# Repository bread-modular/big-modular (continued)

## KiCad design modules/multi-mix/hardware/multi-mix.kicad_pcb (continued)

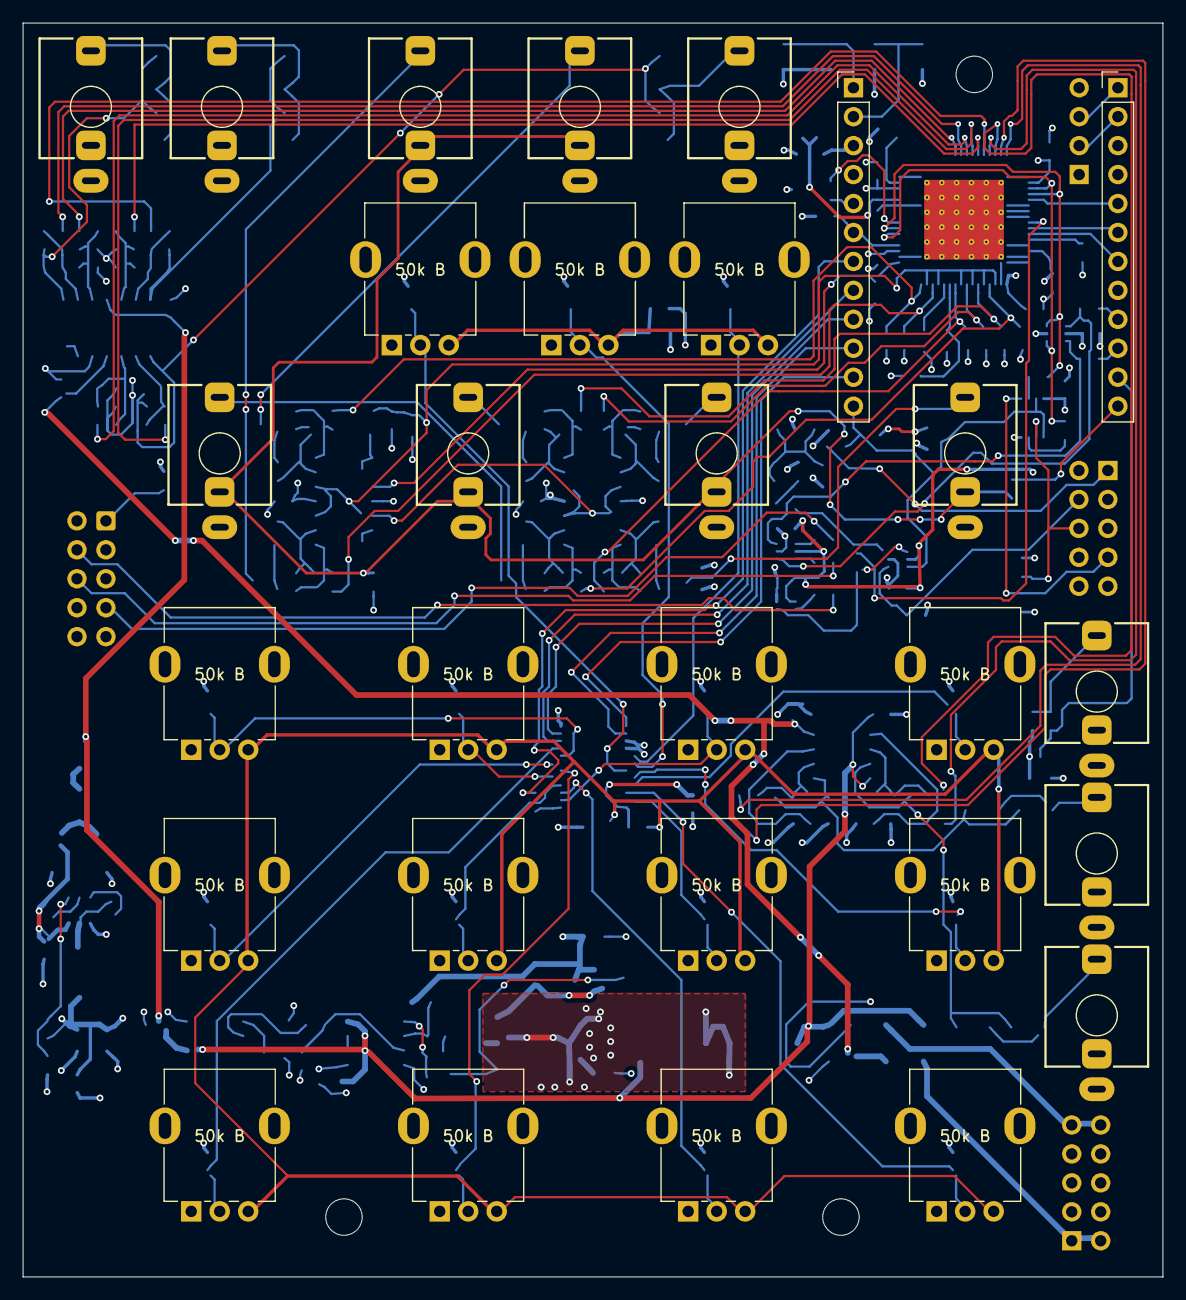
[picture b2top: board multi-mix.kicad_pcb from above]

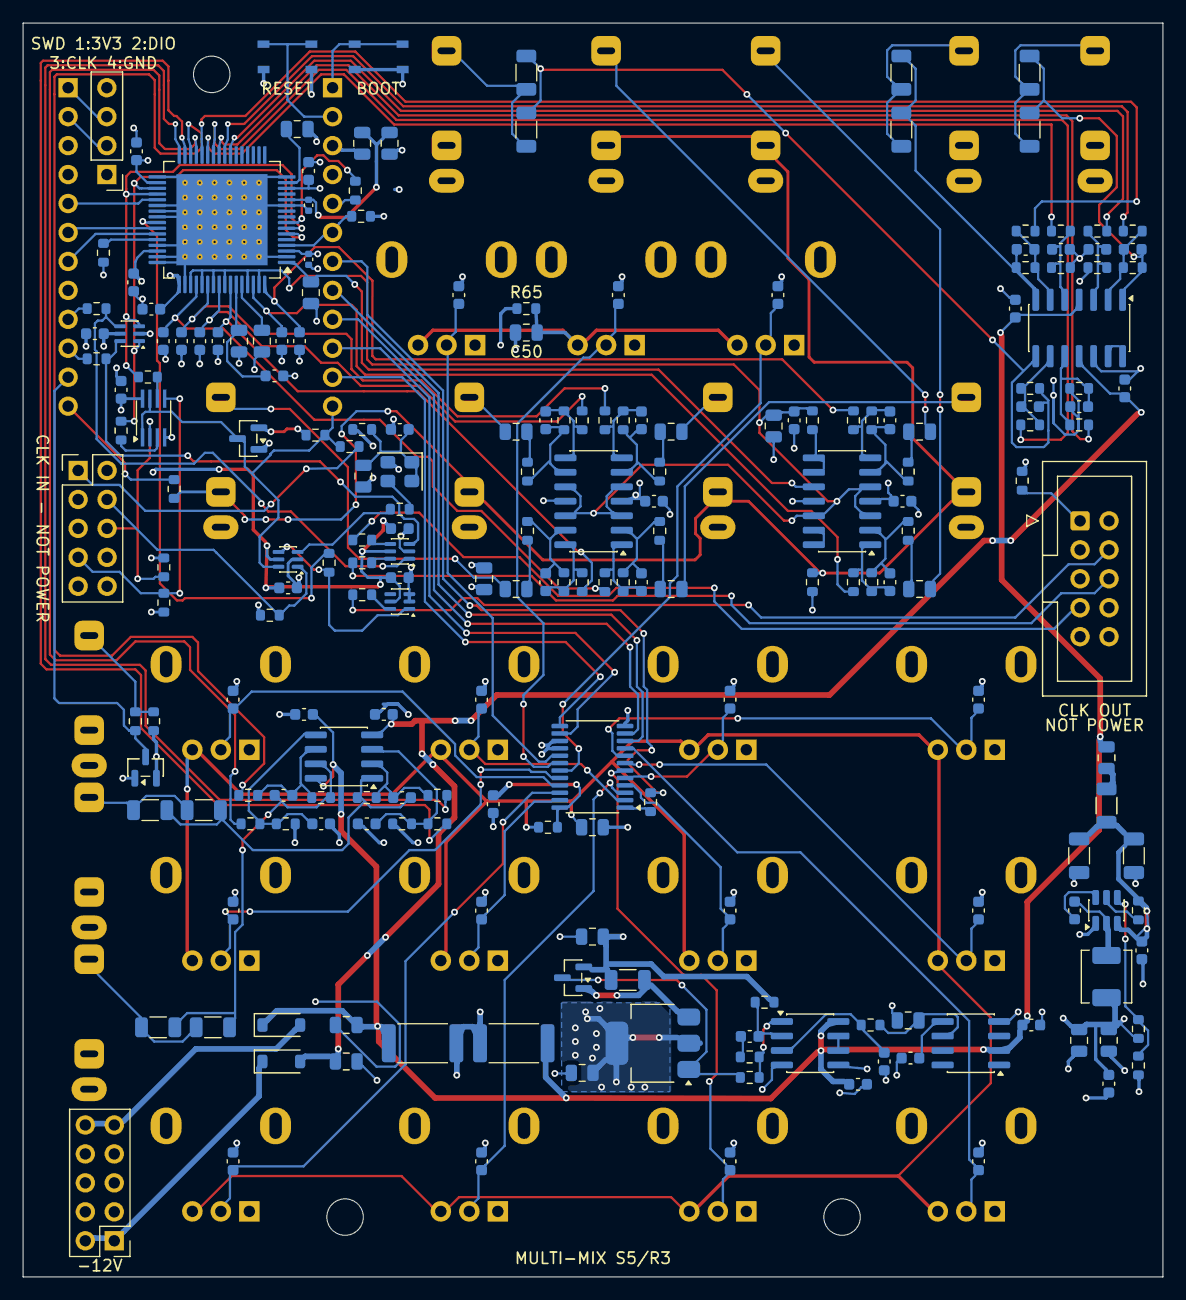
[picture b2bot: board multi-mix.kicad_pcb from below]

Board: 4 copper layers, 100.0 x 110.0 mm, 236 parts (207 on the bottom side), 155 nets.

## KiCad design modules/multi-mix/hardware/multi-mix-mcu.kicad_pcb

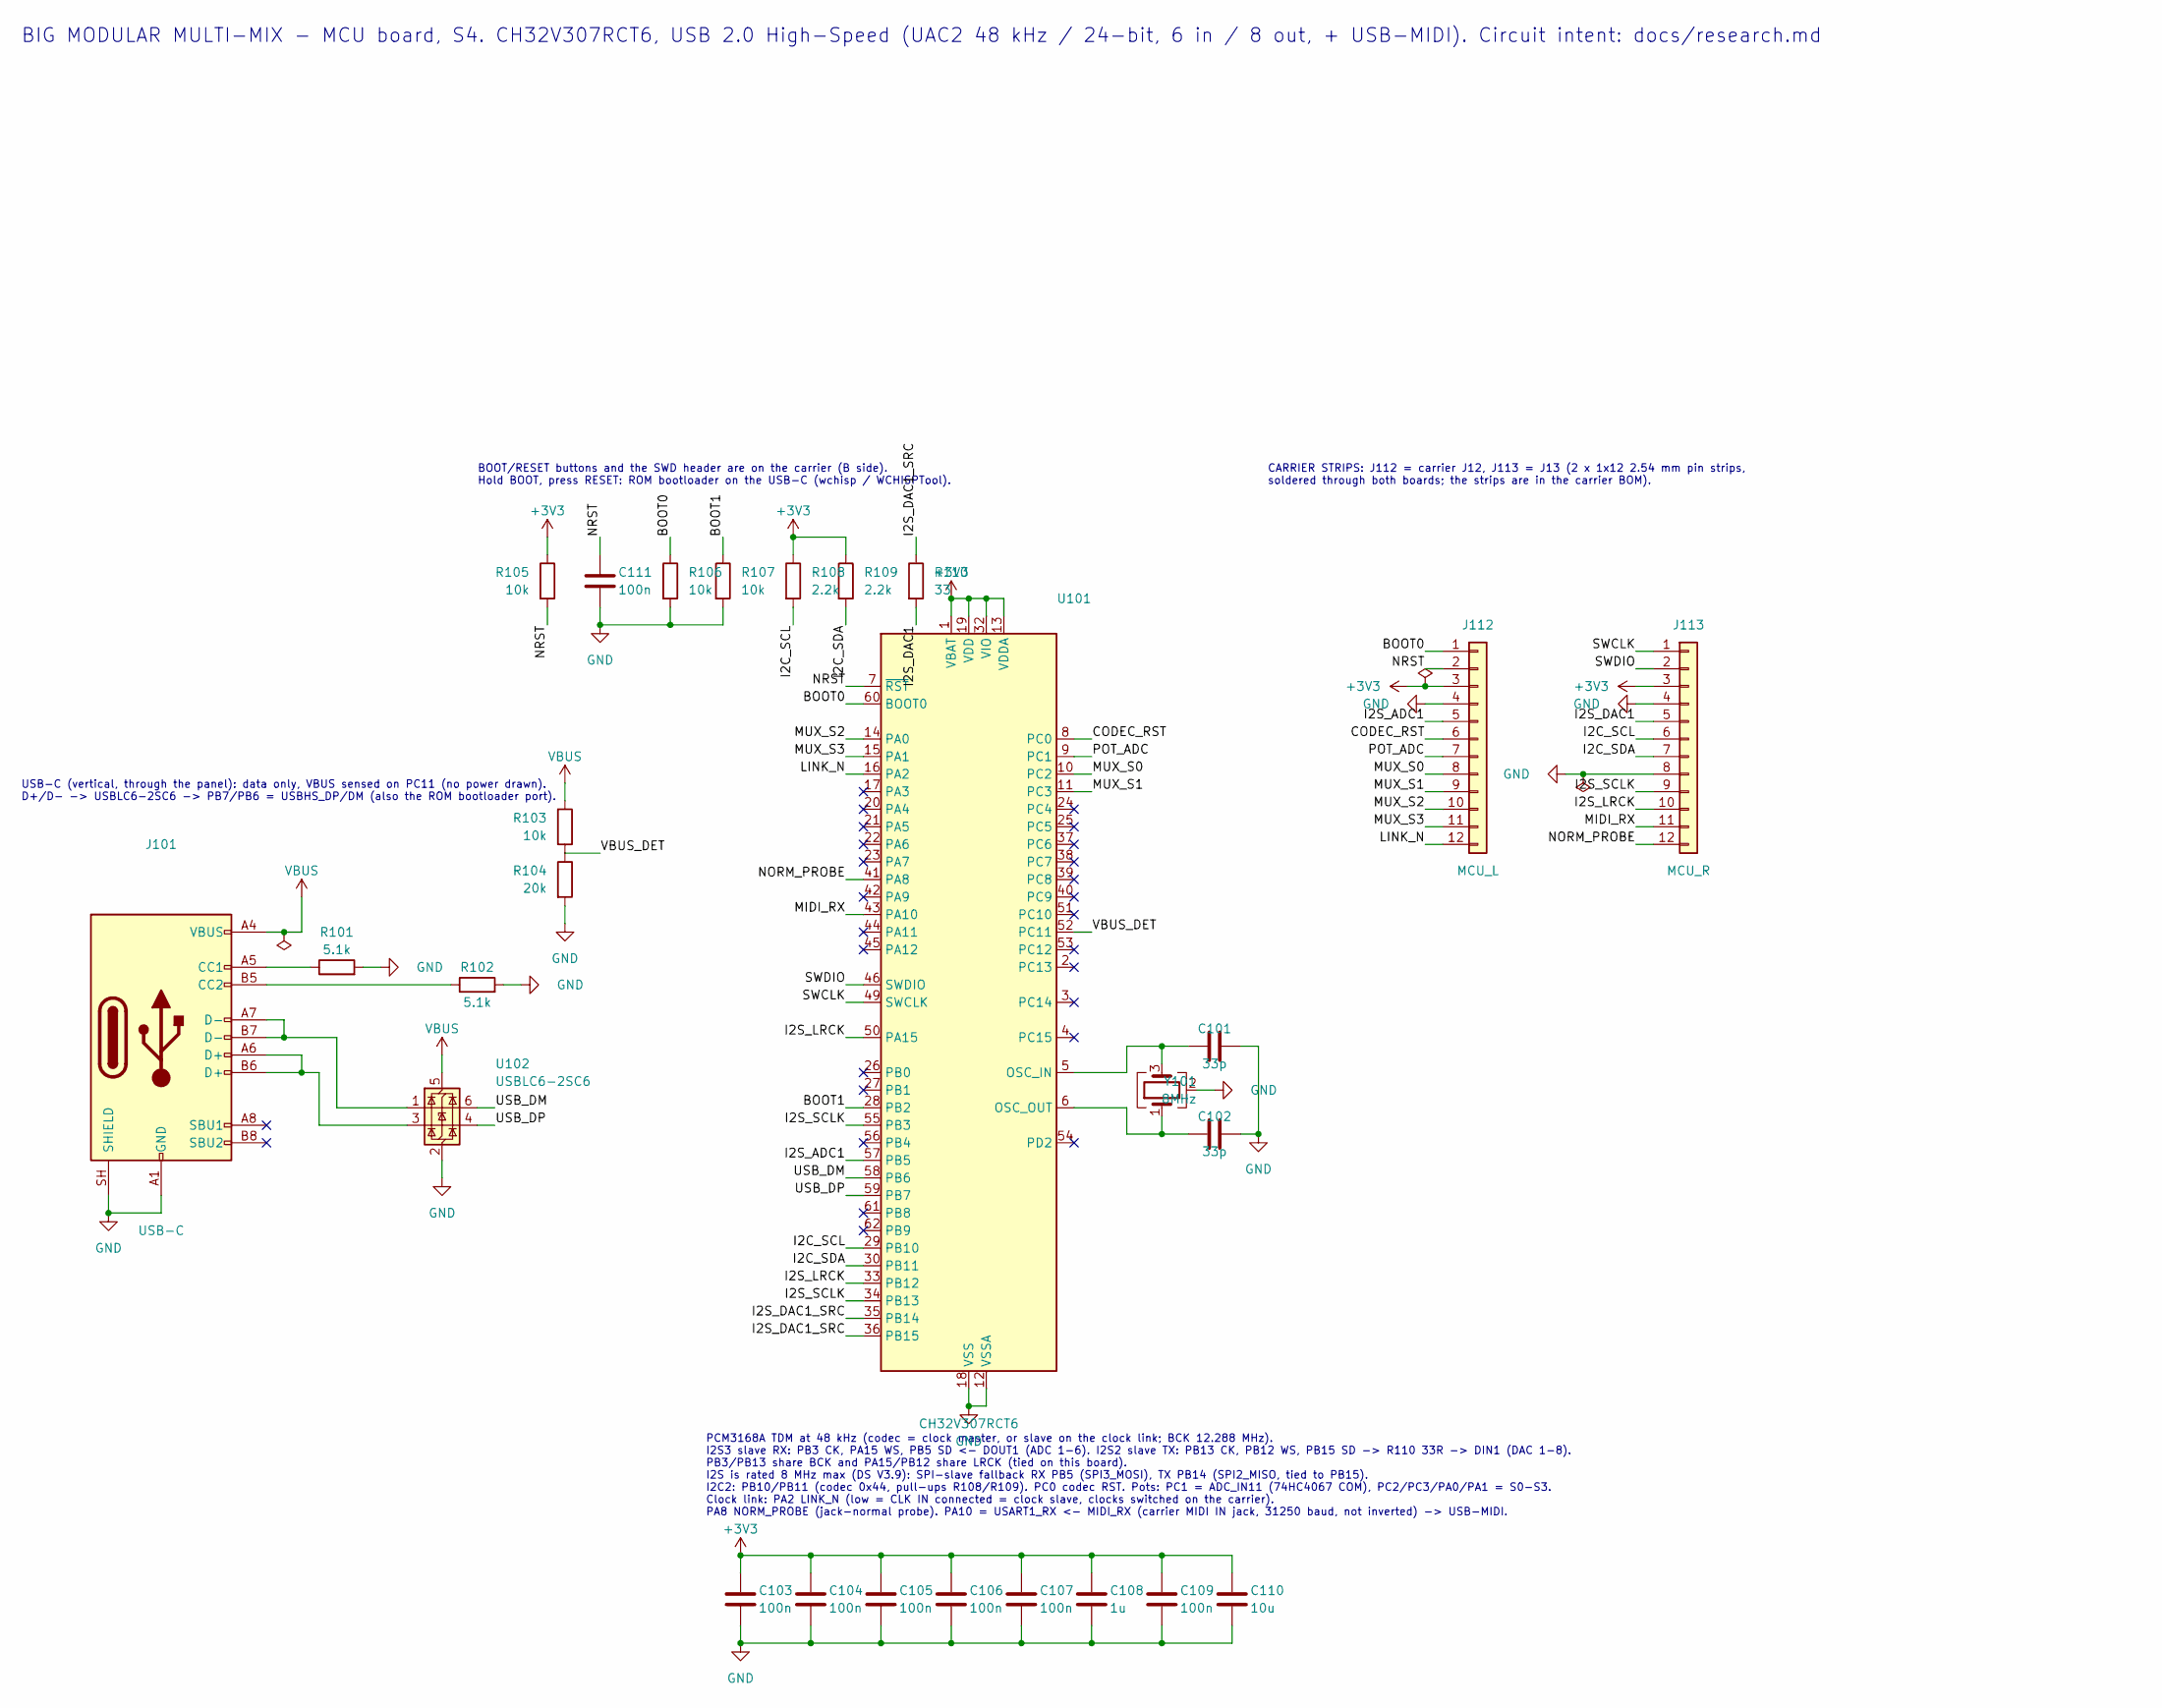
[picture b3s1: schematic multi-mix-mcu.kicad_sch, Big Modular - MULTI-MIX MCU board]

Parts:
C101, C102: 33p; C_0402_1005Metric; Voltage 50V; MPN 0402CG330J500NT; LCSC C1562
C103, C104, C105, C106, C107, C109, C111: 100n; C_0402_1005Metric; Voltage 16V; MPN CL05B104KO5NNNC; LCSC C1525
C108: 1u; C_0402_1005Metric; Voltage 25V; MPN CL05A105KA5NQNC; LCSC C52923
C110: 10u; C_0603_1608Metric; Voltage 10V; MPN CL10A106KP8NNNC; LCSC C19702
J101: USB-C; USB_C_Receptacle_HRO_TYPE-C-31-D-15_Vertical; MPN TYPE-C-31-D-15; LCSC C22464480
J112: MCU_L; PinHeader_1x12_P2.54mm_Vertical
J113: MCU_R; PinHeader_1x12_P2.54mm_Vertical
R101, R102: 5.1k; R_0402_1005Metric; MPN 0402WGF5101TCE; LCSC C25905
R103, R105, R106, R107: 10k; R_0402_1005Metric; MPN 0402WGF1002TCE; LCSC C25744
R104: 20k; R_0402_1005Metric; MPN 0402WGF2002TCE; LCSC C25765
R108, R109: 2.2k; R_0402_1005Metric; MPN 0402WGF2201TCE; LCSC C25879
R110: 33; R_0402_1005Metric; MPN 0402WGF330JTCE; LCSC C25105
U101: CH32V307RCT6; LQFP-64_10x10mm_P0.5mm; MPN CH32V307RCT6; LCSC C2988083
U102: USBLC6-2SC6; SOT-23-6; MPN USBLC6-2SC6; LCSC C7519
Y101: 8MHz; Crystal_SMD_3225-4Pin_3.2x2.5mm; MPN X32258MSB4SI; LCSC C2682774

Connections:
+3V3: C103.1, C104.1, C105.1, C106.1, C107.1, C108.1, C109.1, C110.1, J112.3, J113.3, R105.1, R108.1, R109.1, U101.1 (VBAT), U101.13 (VDDA), U101.19 (VDD), U101.32 (VIO), U101.48 (VDD), U101.64 (VIO)
/BOOT0: J112.1, R106.1, U101.60 (BOOT0)
/BOOT1: R107.1, U101.28 (PB2)
/CODEC_RST: J112.6, U101.8 (PC0)
/I2C_SCL: J113.6, R108.2, U101.29 (PB10)
/I2C_SDA: J113.7, R109.2, U101.30 (PB11)
/I2S_ADC1: J112.5, U101.57 (PB5)
/I2S_DAC1: J113.5, R110.2
/I2S_DAC1_SRC: R110.1, U101.35 (PB14), U101.36 (PB15)
/I2S_LRCK: J113.10, U101.33 (PB12), U101.50 (PA15)
/I2S_SCLK: J113.9, U101.34 (PB13), U101.55 (PB3)
/LINK_N: J112.12, U101.16 (PA2)
/MIDI_RX: J113.11, U101.43 (PA10)
/MUX_S0: J112.8, U101.10 (PC2)
/MUX_S1: J112.9, U101.11 (PC3)
/MUX_S2: J112.10, U101.14 (PA0)
/MUX_S3: J112.11, U101.15 (PA1)
/NORM_PROBE: J113.12, U101.41 (PA8)
/NRST: C111.1, J112.2, R105.2, U101.7 (~RST)
/POT_ADC: J112.7, U101.9 (PC1)
/SWCLK: J113.1, U101.49 (SWCLK)
/SWDIO: J113.2, U101.46 (SWDIO)
/USB_DM: U101.58 (PB6), U102.6 (I/O1)
/USB_DP: U101.59 (PB7), U102.4 (I/O2)
/VBUS_DET: R103.2, R104.1, U101.52 (PC11)
GND: C101.2, C102.2, C103.2, C104.2, C105.2, C106.2, C107.2, C108.2, C109.2, C110.2, C111.2, J101.A1 (GND), J101.A12 (GND), J101.B1 (GND), J101.B12 (GND), J101.SH (SHIELD), J112.4, J113.4, J113.8, R101.2, R102.2, R104.2, R106.2, R107.2, U101.12 (VSSA), U101.18 (VSS), U101.31 (VSS), U101.47 (VSS), U101.63 (VSS), U102.2 (GND), Y101.2 (G), Y101.4 (G)
unnamed: J101.A5 (CC1), R101.1
unnamed: J101.B5 (CC2), R102.1
unnamed: J101.A6 (D+), J101.B6 (D+), U102.3 (I/O2)
unnamed: J101.A7 (D-), J101.B7 (D-), U102.1 (I/O1)
unnamed: C101.1, U101.5 (OSC_IN), Y101.3
unnamed: C102.1, U101.6 (OSC_OUT), Y101.1
VBUS: J101.A4 (VBUS), J101.A9 (VBUS), J101.B4 (VBUS), J101.B9 (VBUS), R103.1, U102.5 (VBUS)

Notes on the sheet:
CARRIER STRIPS: J112 = carrier J12, J113 = J13 (2 x 1x12 2.54 mm pin strips, soldered through both boards; the strips are in the carrier BOM).
PCM3168A TDM at 48 kHz (codec = clock master, or slave on the clock link; BCK 12.288 MHz). I2S3 slave RX: PB3 CK, PA15 WS, PB5 SD <- DOUT1 (ADC 1-6). I2S2 slave TX: PB13 CK, PB12 WS, PB15 SD -> R110 33R -> DIN1 (DAC 1-8). PB3/PB13 share BCK and PA15/PB12 share LRCK (tied on this board). I2S is rate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
USB-C (vertical, through the panel): data only, VBUS sensed on PC11 (no power drawn). D+/D- -> USBLC6-2SC6 -> PB7/PB6 = USBHS_DP/DM (also the ROM bootloader port).
BOOT/RESET buttons and the SWD header are on the carrier (B side). Hold BOOT, press RESET: ROM bootloader on the USB-C (wchisp / WCHISPTool).
BIG MODULAR MULTI-MIX - MCU board, S4. CH32V307RCT6, USB 2.0 High-Speed (UAC2 48 kHz / 24-bit, 6 in / 8 out, + USB-MIDI). Circuit intent: docs/research.md

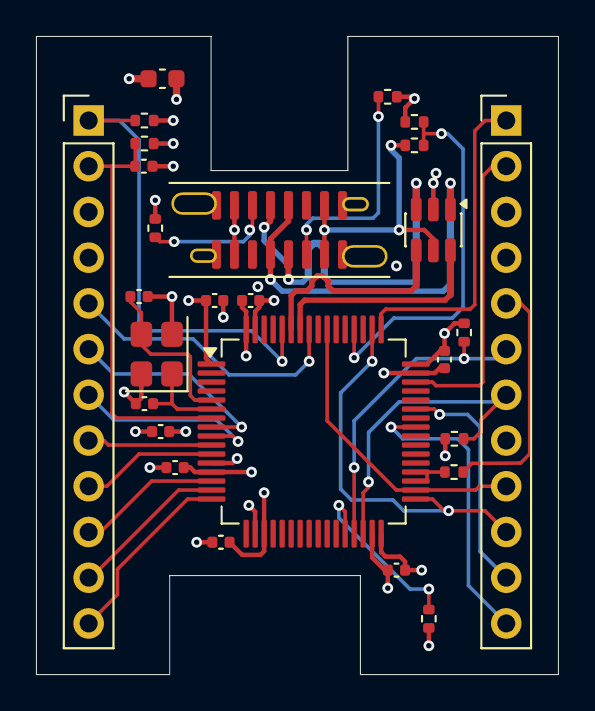
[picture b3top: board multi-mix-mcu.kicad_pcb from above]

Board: 4 copper layers, 29.0 x 35.5 mm, 27 parts (0 on the bottom side), 33 nets.

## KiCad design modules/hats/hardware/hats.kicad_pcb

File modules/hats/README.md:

# HATS

6HP Eurorack hi-hat: Bread Modular NOISE (blue noise, NOISE TONE / BLUE TONE) feeding the
Bread Modular HIHAT (CUTOFF, vactrol VCA, closed-hat DECAY), driven by shared MIDI.
NOISE IN replaces the internal noise through protected jack-contact detection.
Outputs: AUDIO (nominal ~10 Vpp) and HAT CV (intended 0..5 V) with ENV LED.

**S4 schematic (2026-11-08):** one STM32G071C8T6 runs both Bread Modular firmwares; CUTOFF is
read by the ADC and played on a second vactrol by PWM, so CUTOFF and NOISE TONE can be recorded
(REC button + LED at the bottom). **R4** carrier routed by hand for S4 (4 layers, all SMD on the
back, ERC 0 / unconnected 0 / parity 0), **P5** panel with the REC button and LED holes, JLCPCB
re-exported. The new vactrol U11 under NOISE TONE / BLUE TONE adds stacking DRC items that still
need your approval. The STM32 firmware is in `firmware/` (compiled and host-tested, not run on hardware yet).
**R5** (2026-11-09) = R4 copper with fab-review silk fixes: SWD pin legend on J11, larger vactrol
assembly notes clear of the pot pads, `-12V` beside the power header, `HATS R5` board text.
**R6** (2026-11-09) = fab fixes: the MCU's supply, reference and reset caps (C6, C25, C26) moved to
their pins with a local re-route, heat-spreading copper on both sides of the 3.3 V regulator tab
(U1), the U11 vactrol stacking findings approved and excluded like U7's, `HATS R6` board text.

**S3 schematic / R3 routed four-layer carrier / P4 panel.** Recording functionality,
button, LED and associated circuitry have been removed. Pot row spacing is **34 mm**
(previously 24 mm); all pots upright, with the vactrol on the back under CUTOFF (as on
LOW). Copper setback is **1 mm**; all assembled SMD is on the back.

JLCPCB files: `jlcpcb/` (re-exported from S4/R6/P5, 2026-11-09). See `jlcpcb/README.md`, `docs/research.md` and
`docs/noise-in-protection.md`. Exported, not supplier-accepted or bench-validated.
Firmware clock/reference settings were left unchanged at the user's request.

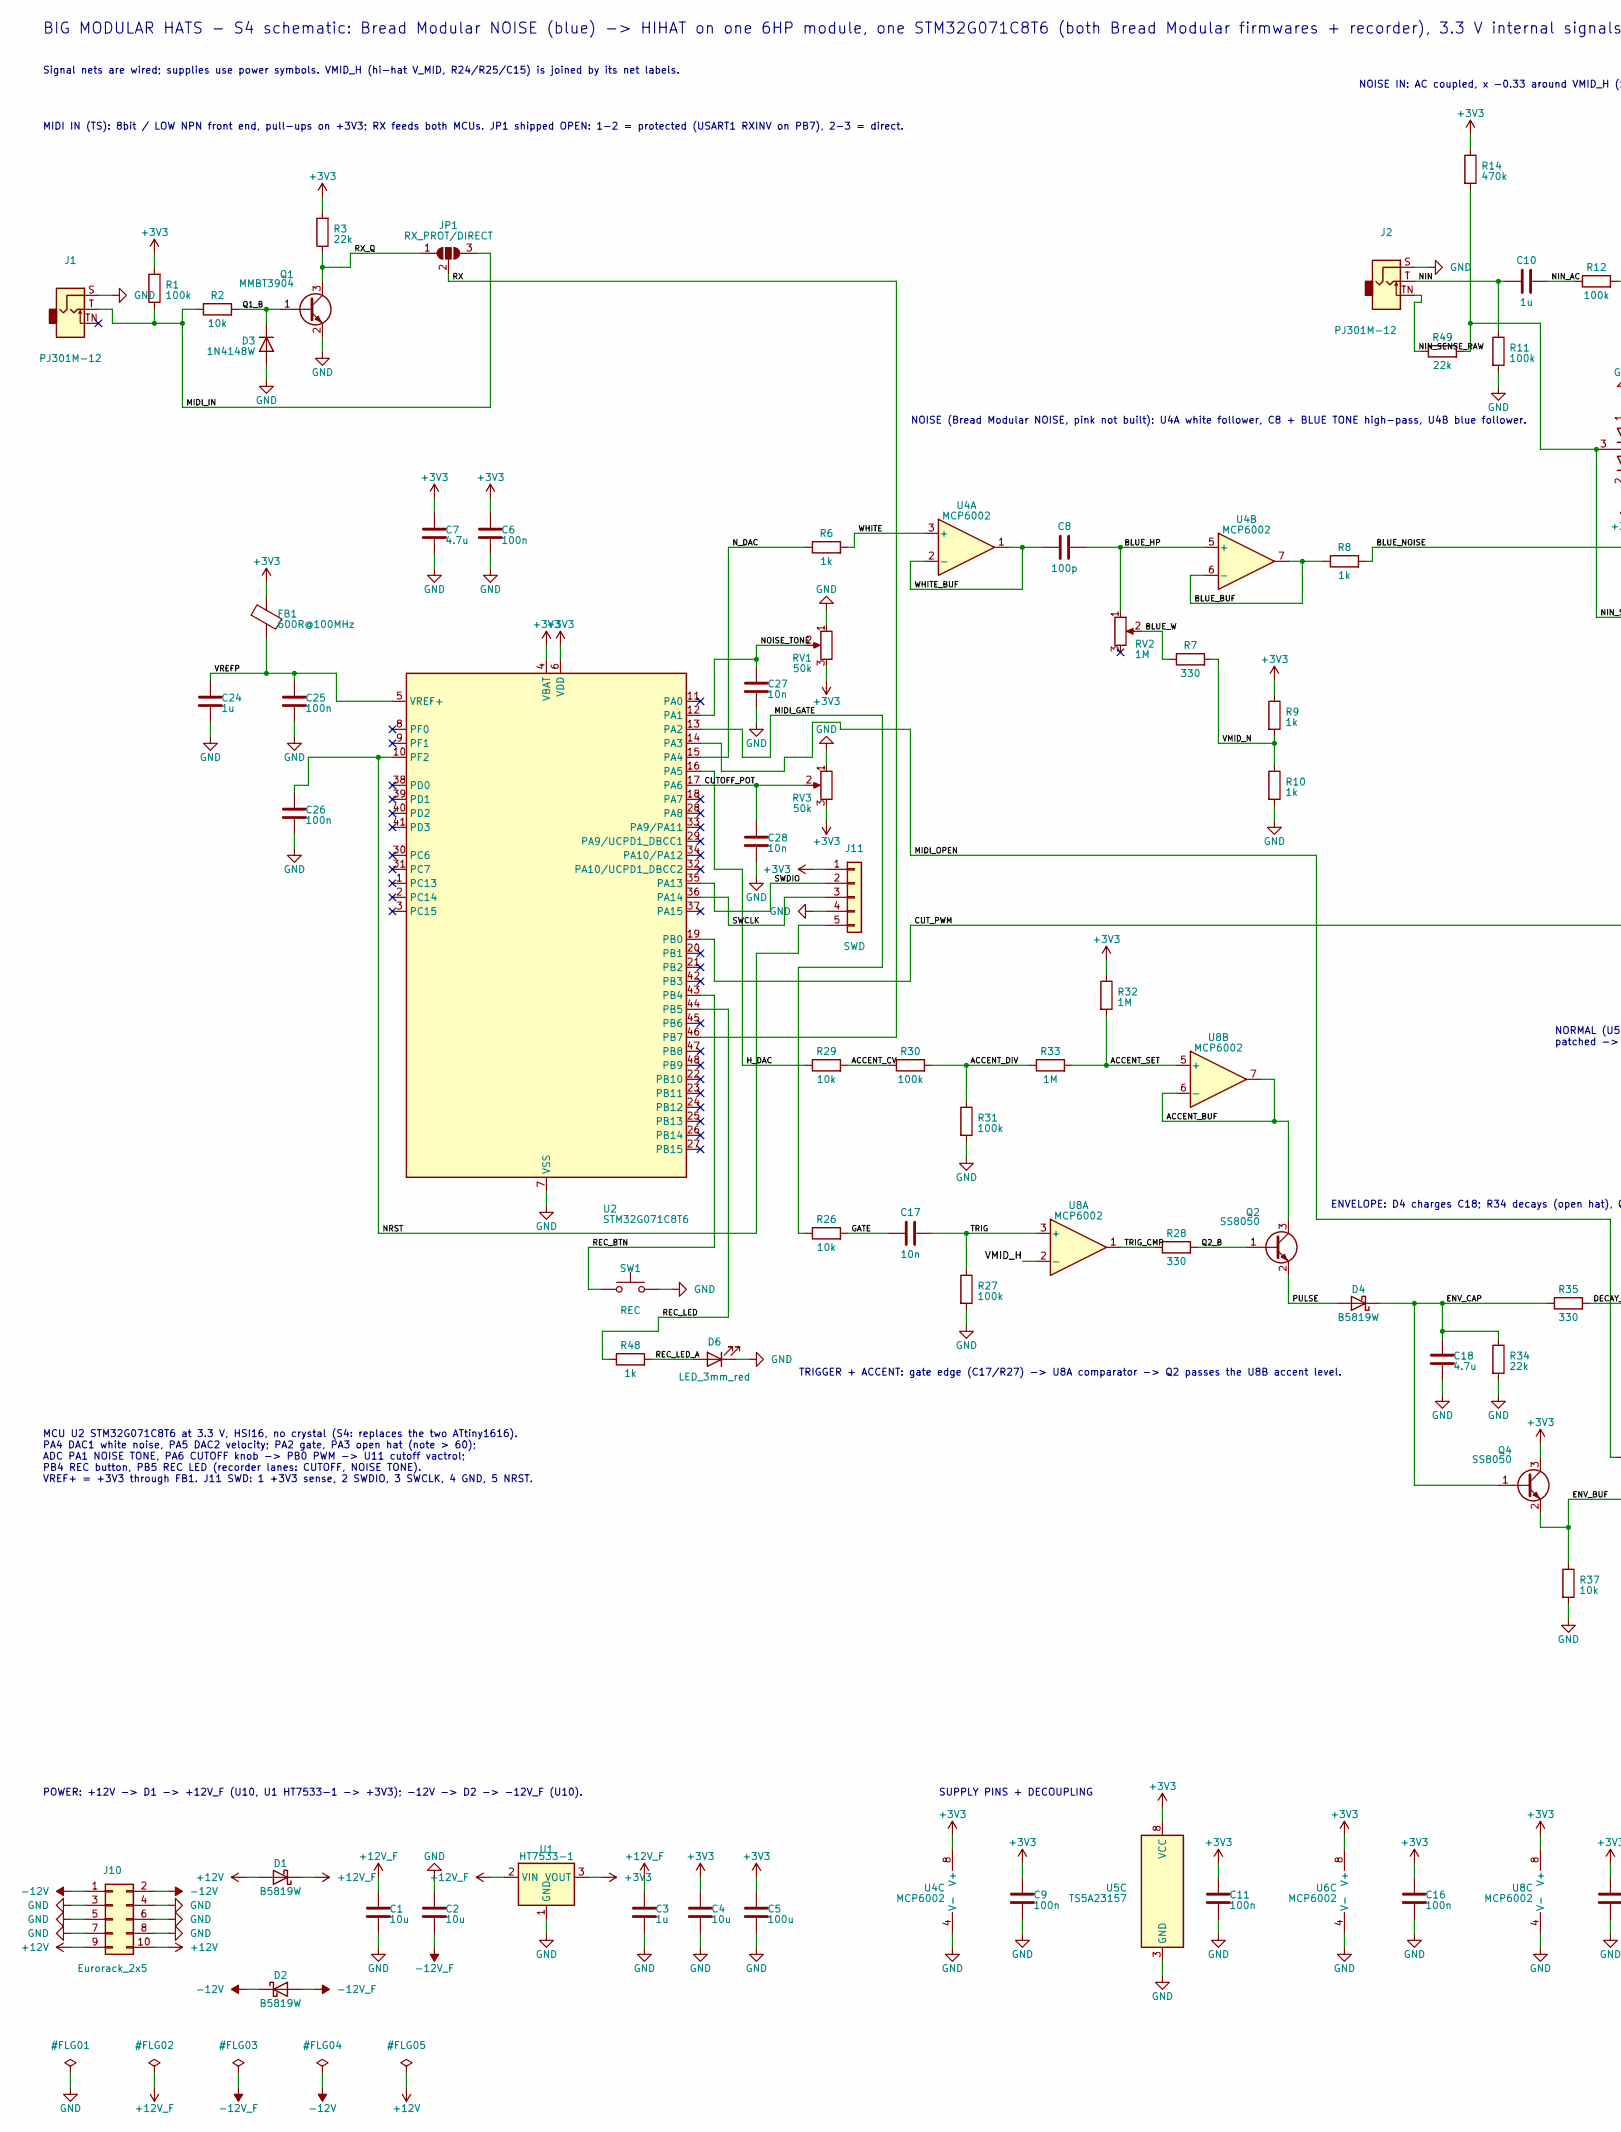
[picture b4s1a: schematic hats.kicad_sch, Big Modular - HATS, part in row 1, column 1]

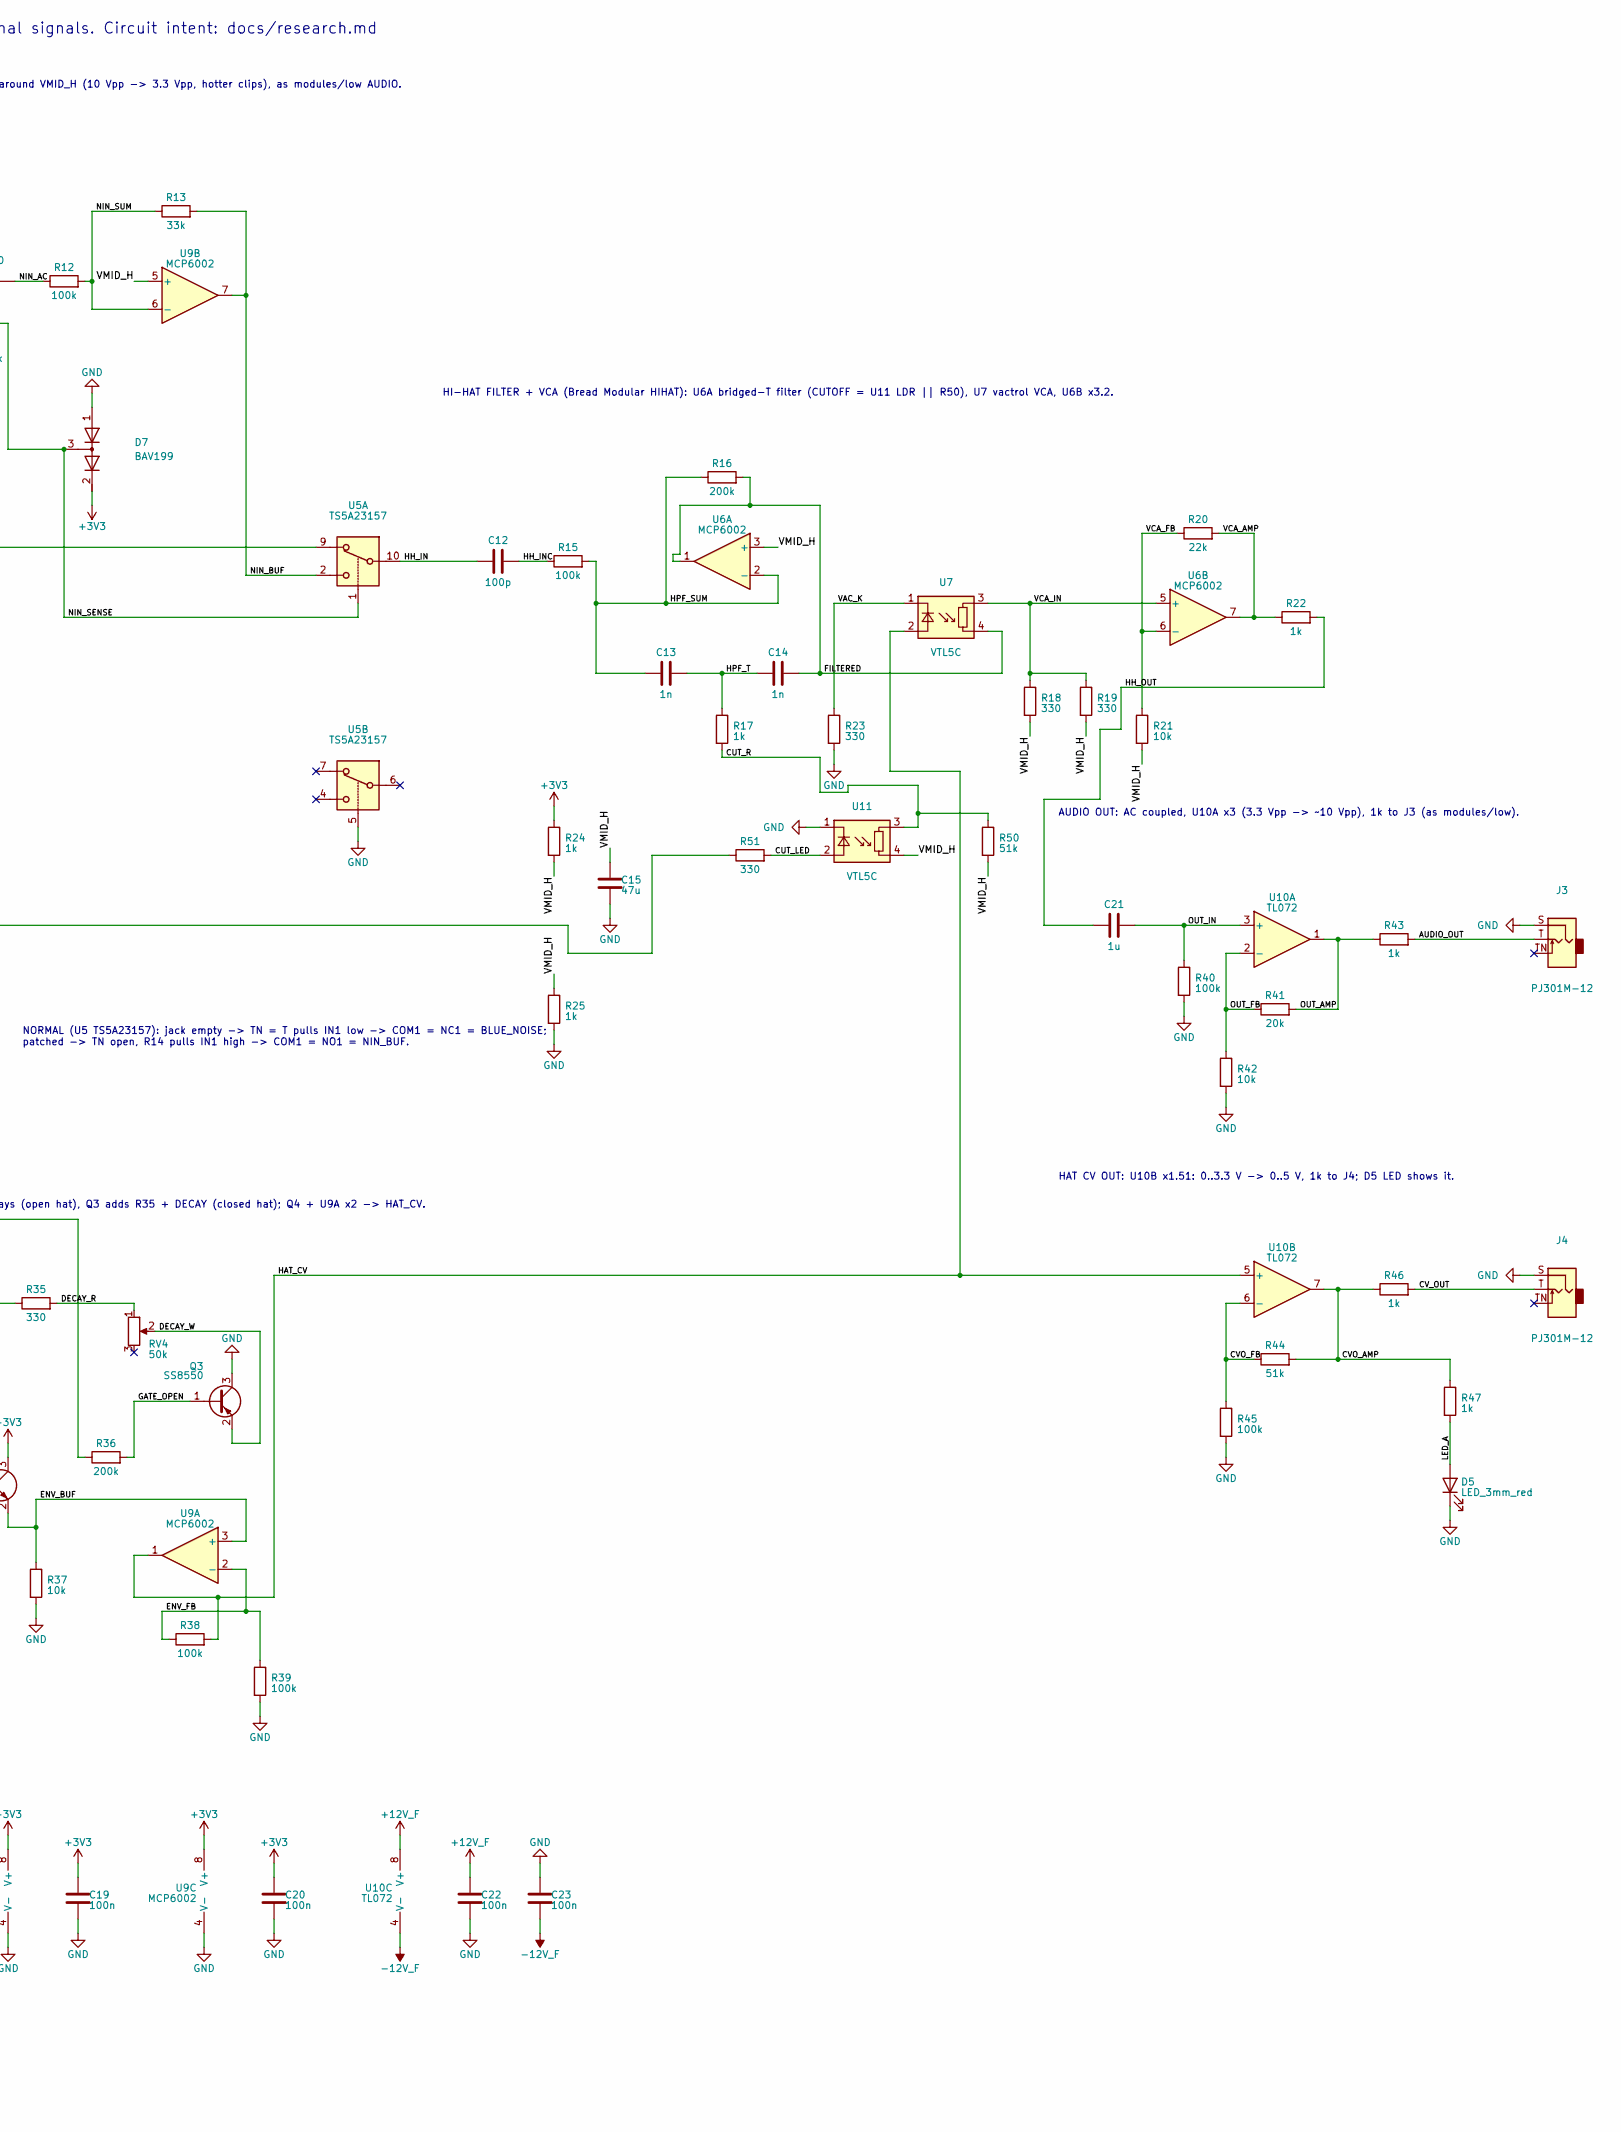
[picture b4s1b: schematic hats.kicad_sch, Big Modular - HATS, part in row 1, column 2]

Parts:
C1, C2, C4: 10u; C_0805_2012Metric; Voltage 25V; MPN CL21A106KAYNNNE; LCSC C15850
C3, C10, C24: 1u; C_0805_2012Metric; Voltage 50V; MPN CL21B105KBFNNNE; LCSC C28323
C5: 100u; C_1206_3216Metric; Voltage 6.3V; MPN CL31A107MQHNNNE; LCSC C15008
C6, C9, C11, C16, C19, C20, C22, C23, C25, C26: 100n; C_0603_1608Metric; Voltage 50V; MPN CC0603KRX7R9BB104; LCSC C14663
C7, C18: 4.7u; C_0603_1608Metric; Voltage 16V; MPN CL10A475KO8NNNC; LCSC C19666
C8, C12: 100p; C_0603_1608Metric; Voltage 50V; MPN CL10C101JB8NNNC; LCSC C14858
C13, C14: 1n; C_0603_1608Metric; Voltage 50V; MPN CL10B102KB8NNNC; LCSC C1588
C15: 47u; C_0805_2012Metric; Voltage 6.3V; MPN CL21A476MQYNNNE; LCSC C16780
C17, C27, C28: 10n; C_0603_1608Metric; Voltage 50V; MPN 0603B103K500NT; LCSC C57112
C21: 1u; C_0805_2012Metric; Voltage 25V; MPN CL21B105KBFNNNE; LCSC C28323
D1, D2, D4: B5819W; D_SOD-123; MPN B5819W SL; LCSC C8598
D3: 1N4148W; D_SOD-123; MPN 1N4148W; LCSC C81598
D5, D6: LED_3mm_red; LED_D3.0mm
D7: BAV199; SOT-23; MPN BAV199,215; LCSC C40919
FB1: 600R@100MHz; L_0603_1608Metric; MPN GZ1608D601TF; LCSC C1002
J1, J2, J3, J4: PJ301M-12; Jack_3.5mm_QingPu_WQP-PJ301M-12_Vertical
J10: Eurorack_2x5; PinHeader_2x05_P2.54mm_Vertical
J11: SWD; PinHeader_1x05_P2.54mm_Vertical
JP1: RX_PROT/DIRECT; SolderJumper-3_P1.3mm_Open_RoundedPad1.0x1.5mm
Q1: MMBT3904; SOT-23; MPN MMBT3904(RANGE:100-300); LCSC C20526
Q2, Q4: SS8050; SOT-23; MPN SS8050; LCSC C431710
Q3: SS8550; SOT-23; MPN SS8550; LCSC C364314
R1, R11, R12, R15, R27, R30, R31, R38, R39, R40, R45: 100k; R_0603_1608Metric; MPN 0603WAF1003T5E; LCSC C25803
R2, R21, R26, R29, R37, R42: 10k; R_0603_1608Metric; MPN 0603WAF1002T5E; LCSC C25804
R3, R20, R34, R49: 22k; R_0603_1608Metric; MPN 0603WAF2202T5E; LCSC C31850
R6, R8, R9, R10, R17, R22, R24, R25, R47, R48: 1k; R_0603_1608Metric; MPN 0603WAF1001T5E; LCSC C21190
R7, R18, R19, R23, R28, R35, R51: 330; R_0603_1608Metric; MPN 0603WAF3300T5E; LCSC C23138
R13: 33k; R_0603_1608Metric; MPN 0603WAF3302T5E; LCSC C4216
R14: 470k; R_0603_1608Metric; MPN 0603WAF4703T5E; LCSC C23178
R16, R36: 200k; R_0603_1608Metric; MPN 0603WAF2003T5E; LCSC C25811
R32, R33: 1M; R_0603_1608Metric; MPN 0603WAF1004T5E; LCSC C22935
R41: 20k; R_0603_1608Metric; MPN 0603WAF2002T5E; LCSC C4184
R43, R46: 1k; R_1206_3216Metric; MPN ESR18EZPF1001; LCSC C2074262
R44, R50: 51k; R_0603_1608Metric; MPN 0603WAF5102T5E; LCSC C23196
RV1, RV3, RV4: 50k; Potentiometer_RV09
RV2: 1M; Potentiometer_RV09
SW1: REC; SW_PUSH_6mm_H7.3mm; MPN 6x6x7 mm THT tact switch, 4 pins (gener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
U1: HT7533-1; SOT-89-3; MPN HT7533-1; LCSC C14289
U2: STM32G071C8T6; LQFP-48_7x7mm_P0.5mm; MPN STM32G071C8T6; LCSC C529341
U4, U6, U8, U9: MCP6002; SOIC-8_3.9x4.9mm_P1.27mm; MPN MCP6002T-I/SN; LCSC C7377
U5: TS5A23157; TSSOP-10_3x3mm_P0.5mm; MPN TS5A23157DGSR; LCSC C11133
U7, U11: VTL5C
U10: TL072; SOIC-8_3.9x4.9mm_P1.27mm; MPN TL072CDT; LCSC C6961

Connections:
+3V3: C4.1, C5.1, C6.1, C7.1, C9.1, C11.1, C16.1, C19.1, C20.1, D7.2 (K), FB1.1, J11.1, Q4.3 (C), R1.2, R3.2, R9.1, R14.1, R24.1, R32.1, RV1.3, RV3.3, U1.3 (VOUT), U2.4 (VBAT), U2.6 (VDD), U4.8 (V+), U5.8 (VCC), U6.8 (V+), U8.8 (V+), U9.8 (V+)
+12V: D1.2 (A), J10.9, J10.10
+12V_F: C1.1, C3.1, C22.1, D1.1 (K), U1.2 (VIN), U10.8 (V+)
-12V: D2.1 (K), J10.1, J10.2
-12V_F: C2.2, C23.2, D2.2 (A), U10.4 (V-)
/ACCENT_BUF: Q2.3 (C), U8.6 (-), U8.7
/ACCENT_CV: R29.2, R30.1
/ACCENT_DIV: R30.2, R31.1, R33.1
/ACCENT_SET: R32.2, R33.2, U8.5 (+)
/AUDIO_OUT: J3.T, R43.2
/BLUE_BUF: R8.1, U4.6 (-), U4.7
/BLUE_HP: C8.2, RV2.1, U4.5 (+)
/BLUE_NOISE: R8.2, U5.9
/BLUE_W: R7.1, RV2.2
/CUTOFF_POT: C28.1, RV3.2, U2.17 (PA6)
/CUT_LED: R51.2, U11.2 (+)
/CUT_PWM: R51.1, U2.19 (PB0)
/CUT_R: R17.2, R50.1, U11.3
/CVO_AMP: R44.2, R46.1, R47.1, U10.7
/CVO_FB: R44.1, R45.1, U10.6 (-)
/CV_OUT: J4.T, R46.2
/DECAY_R: R35.2, RV4.1
/DECAY_W: Q3.2 (E), RV4.2
/ENV_BUF: Q4.2 (E), R37.1, U9.3 (+)
/ENV_CAP: C18.1, D4.1 (K), Q4.1 (B), R34.1, R35.1
/ENV_FB: R38.1, R39.1, U9.2 (-)
/FILTERED: C14.2, R16.2, U6.1, U7.4
/GATE: C17.1, R26.2
/GATE_OPEN: Q3.1 (B), R36.2
/HAT_CV: R38.2, U7.2 (+), U9.1, U10.5 (+)
/HH_IN: C12.1, U5.10
/HH_INC: C12.2, R15.1
/HH_OUT: C21.1, R22.2
/HPF_SUM: C13.1, R15.2, R16.1, U6.2 (-)
/HPF_T: C13.2, C14.1, R17.1
/H_DAC: R29.1, U2.16 (PA5)
/LED_A: D5.2 (A), R47.2
/MIDI_GATE: R26.1, U2.13 (PA2)
/MIDI_IN: J1.T, JP1.3 (B), R1.1, R2.1
/MIDI_OPEN: R36.1, U2.14 (PA3)
/NIN: C10.1, J2.T, R11.1
/NIN_AC: C10.2, R12.1
/NIN_BUF: R13.2, U5.2, U9.7
/NIN_SENSE: D7.3 (common), R14.2, R49.2, U5.1
/NIN_SENSE_RAW: J2.TN, R49.1
/NIN_SUM: R12.2, R13.1, U9.6 (-)
/NOISE_TONE: C27.1, RV1.2, U2.12 (PA1)
/NRST: C26.1, J11.5, U2.10 (PF2)
/N_DAC: R6.1, U2.15 (PA4)
/OUT_AMP: R41.2, R43.1, U10.1
/OUT_FB: R41.1, R42.1, U10.2 (-)
/OUT_IN: C21.2, R40.1, U10.3 (+)
/PULSE: D4.2 (A), Q2.2 (E)
/Q1_B: D3.1 (K), Q1.1 (B), R2.2
/Q2_B: Q2.1 (B), R28.2
/REC_BTN: SW1.1, U2.43 (PB4)
/REC_LED: R48.1, U2.44 (PB5)
/REC_LED_A: D6.2 (A), R48.2
/RX: JP1.2 (C), U2.46 (PB7)
/RX_Q: JP1.1 (A), Q1.3 (C), R3.1
/SWCLK: J11.3, U2.36 (PA14)
/SWDIO: J11.2, U2.35 (PA13)
/TRIG: C17.2, R27.1, U8.3 (+)
/TRIG_CMP: R28.1, U8.1
/VAC_K: R23.1, U7.1 (-)
/VCA_AMP: R20.2, R22.1, U6.7
/VCA_FB: R20.1, R21.1, U6.6 (-)
/VCA_IN: R18.1, R19.1, U6.5 (+), U7.3
/VMID_H: C15.1, R18.2, R19.2, R21.2, R24.2, R25.1, R50.2, U6.3 (+), U8.2 (-), U9.5 (+), U11.4
/VMID_N: R7.2, R9.2, R10.1
/VREFP: C24.1, C25.1, FB1.2, U2.5 (VREF+)
/WHITE: R6.2, U4.3 (+)
/WHITE_BUF: C8.1, U4.1, U4.2 (-)
GND: C1.2, C2.1, C3.2, C4.2, C5.2, C6.2, C7.2, C9.2, C11.2, C15.2, C16.2, C18.2, C19.2, C20.2, C22.2, C23.1, C24.2, C25.2, C26.2, C27.2, C28.2, D3.2 (A), D5.1 (K), D6.1 (K), D7.1 (A), J1.S, J2.S, J3.S, J4.S, J10.3, J10.4, J10.5, J10.6, J10.7, J10.8, J11.4, Q1.2 (E), Q3.3 (C), R10.2, R11.2, R23.2, R25.2, R27.2, R31.2, R34.2, R37.2, R39.2, R40.2, R42.2, R45.2, RV1.1, RV3.1, SW1.2, U1.1 (GND), U2.7 (VSS), U4.4 (V-), U5.3 (GND), U5.5, U6.4 (V-), U8.4 (V-), U9.4 (V-), U11.1 (-)

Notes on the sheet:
SUPPLY PINS + DECOUPLING
HI-HAT FILTER + VCA (Bread Modular HIHAT): U6A bridged-T filter (CUTOFF = U11 LDR || R50), U7 vactrol VCA, U6B x3.2.
Signal nets are wired; supplies use power symbols. VMID_H (hi-hat V_MID, R24/R25/C15) is joined by its net labels.
BIG MODULAR HATS - S4 schematic: Bread Modular NOISE (blue) -> HIHAT on one 6HP module, one STM32G071C8T6 (both Bread Modular firmwares + recorder), 3.3 V internal signals. Circuit intent: docs/research.md
AUDIO OUT: AC coupled, U10A x3 (3.3 Vpp -> ~10 Vpp), 1k to J3 (as modules/low).
ENVELOPE: D4 charges C18; R34 decays (open hat), Q3 adds R35 + DECAY (closed hat); Q4 + U9A x2 -> HAT_CV.
HAT CV OUT: U10B x1.51: 0..3.3 V -> 0..5 V, 1k to J4; D5 LED shows it.
TRIGGER + ACCENT: gate edge (C17/R27) -> U8A comparator -> Q2 passes the U8B accent level.
MCU U2 STM32G071C8T6 at 3.3 V, HSI16, no crystal (S4: replaces the two ATtiny1616). PA4 DAC1 white noise, PA5 DAC2 velocity; PA2 gate, PA3 open hat (note > 60); ADC PA1 NOISE TONE, PA6 CUTOFF knob -> PB0 PWM -> U11 cutoff vactrol; PB4 REC button, PB5 REC LED (recorder lanes: CUTOFF, NOISE TONE). VR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
NOISE IN: AC coupled, x -0.33 around VMID_H (10 Vpp -> 3.3 Vpp, hotter clips), as modules/low AUDIO.
POWER: +12V -> D1 -> +12V_F (U10, U1 HT7533-1 -> +3V3); -12V -> D2 -> -12V_F (U10).
NOISE (Bread Modular NOISE, pink not built): U4A white follower, C8 + BLUE TONE high-pass, U4B blue follower.
NORMAL (U5 TS5A23157): jack empty -> TN = T pulls IN1 low -> COM1 = NC1 = BLUE_NOISE; patched -> TN open, R14 pulls IN1 high -> COM1 = NO1 = NIN_BUF.
MIDI IN (TS): 8bit / LOW NPN front end, pull-ups on +3V3; RX feeds both MCUs. JP1 shipped OPEN: 1-2 = protected (USART1 RXINV on PB7), 2-3 = direct.
